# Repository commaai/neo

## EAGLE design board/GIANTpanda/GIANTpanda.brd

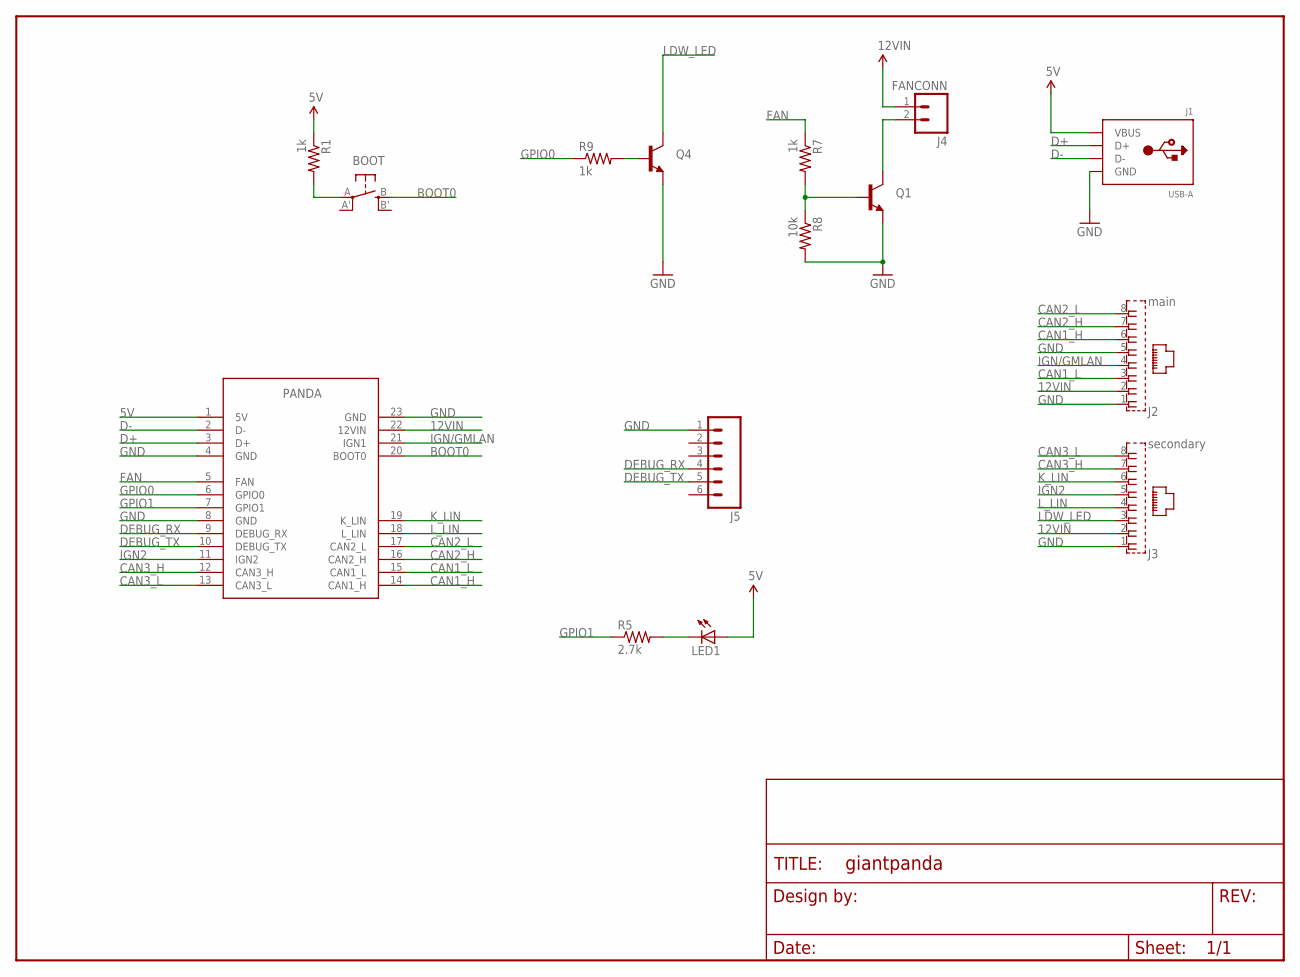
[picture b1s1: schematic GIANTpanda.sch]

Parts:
BOOT: SPST_TACT-EVQQ2; EVQ-Q2
FRAME1: FRAME-LETTERNO_PACKAGE; DUMMY
J1: USB-A; MOLEX_480371000
J2: main; GLX-S-88M
J3: secondary; GLX-S-88M
J4: FANCONN; 1.25CONN
J5: M06NO_SILK_YES_STOP; 1X06_NO_SILK_YES_STOP
LED1: LEDCHIPLED_0805; CHIPLED_0805
Q1, Q4: MMBT2222A; SOT23-3
R1, R7, R9: 1k; 0603-R
R5: 2.7k; 0603-R
R8: 10k; 0603-R
U$1: PANDA; PANDA-FOOT

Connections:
5V: J1.1 (VBUS), LED1.A, R1.1, U$1.1 (5V)
12VIN: J2.2, J3.2, J4.1, U$1.22 (12VIN)
BOOT0: BOOT.B (S), U$1.20 (BOOT0)
CAN1_H: J2.6, U$1.14 (CAN1_H)
CAN1_L: J2.3, U$1.15 (CAN1_L)
CAN2_H: J2.7, U$1.16 (CAN2_H)
CAN2_L: J2.8, U$1.17 (CAN2_L)
CAN3_H: J3.7, U$1.12 (CAN3_H)
CAN3_L: J3.8, U$1.13 (CAN3_L)
D+: J1.3 (D+), U$1.3 (D+)
D-: J1.2 (D-), U$1.2 (D-)
DEBUG_RX: J5.4, U$1.9 (DEBUG_RX)
DEBUG_TX: J5.5, U$1.10 (DEBUG_TX)
FAN: R7.1, U$1.5 (FAN)
GND: J1.4 (GND), J2.1, J2.5, J3.1, J5.1, Q1.2 (E), Q4.2 (E), R8.2, U$1.4 (GND), U$1.8 (GND), U$1.23 (GND)
GPIO0: R9.1, U$1.6 (GPIO0)
GPIO1: R5.1, U$1.7 (GPIO1)
IGN2: J3.5, U$1.11 (IGN2)
IGN/GMLAN: J2.4, U$1.21 (IGN1)
K_LIN: J3.6, U$1.19 (K_LIN)
LDW_LED: J3.3, Q4.3 (C)
L_LIN: J3.4, U$1.18 (L_LIN)
unnamed: BOOT.A, R1.2
unnamed: LED1.C, R5.2
unnamed: J4.2, Q1.3 (C)
unnamed: Q1.1 (B), R7.2, R8.1
unnamed: Q4.1 (B), R9.2

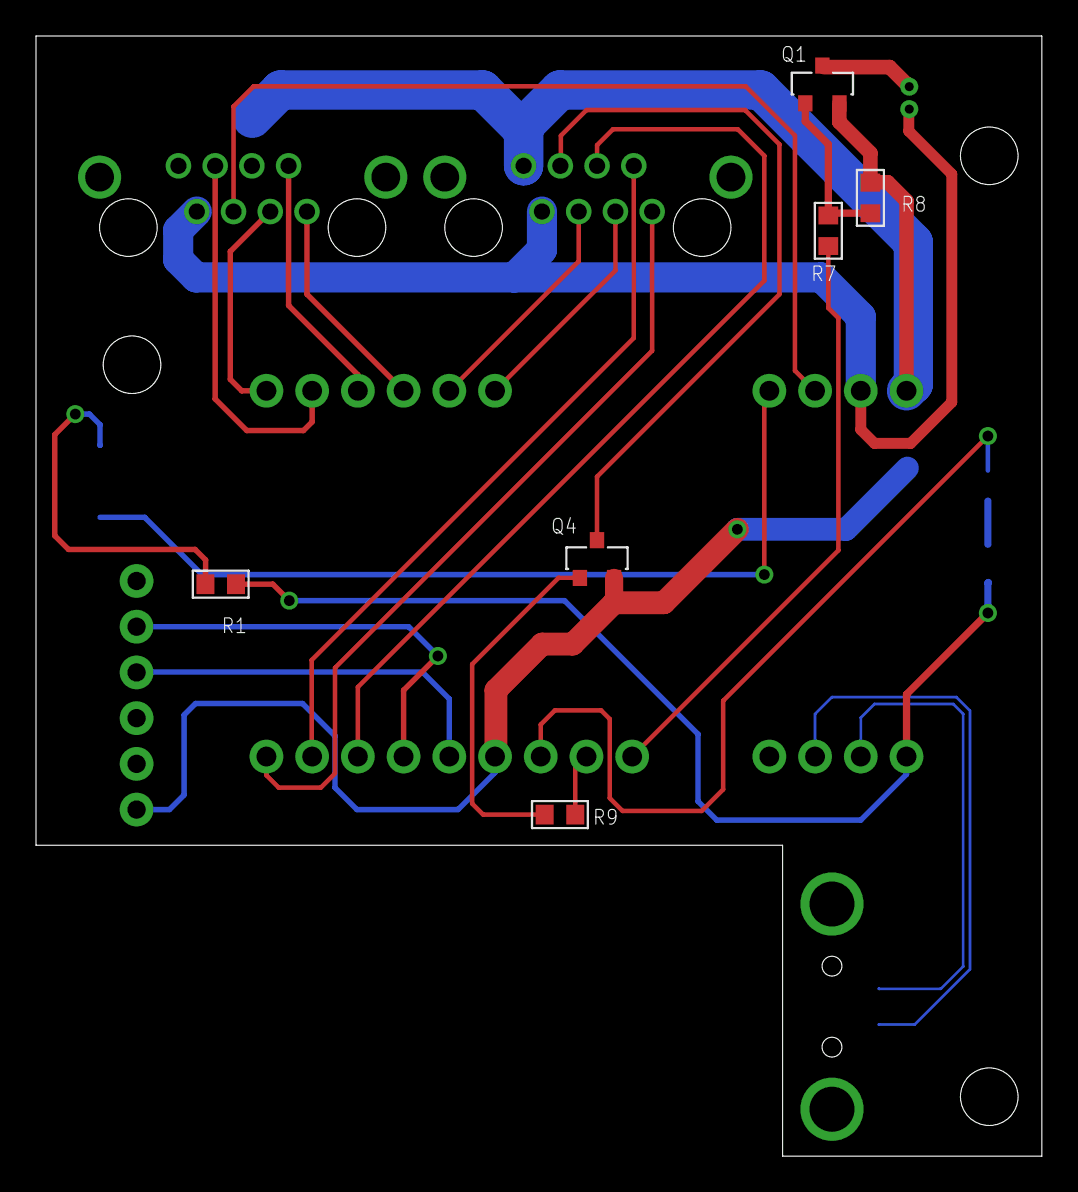
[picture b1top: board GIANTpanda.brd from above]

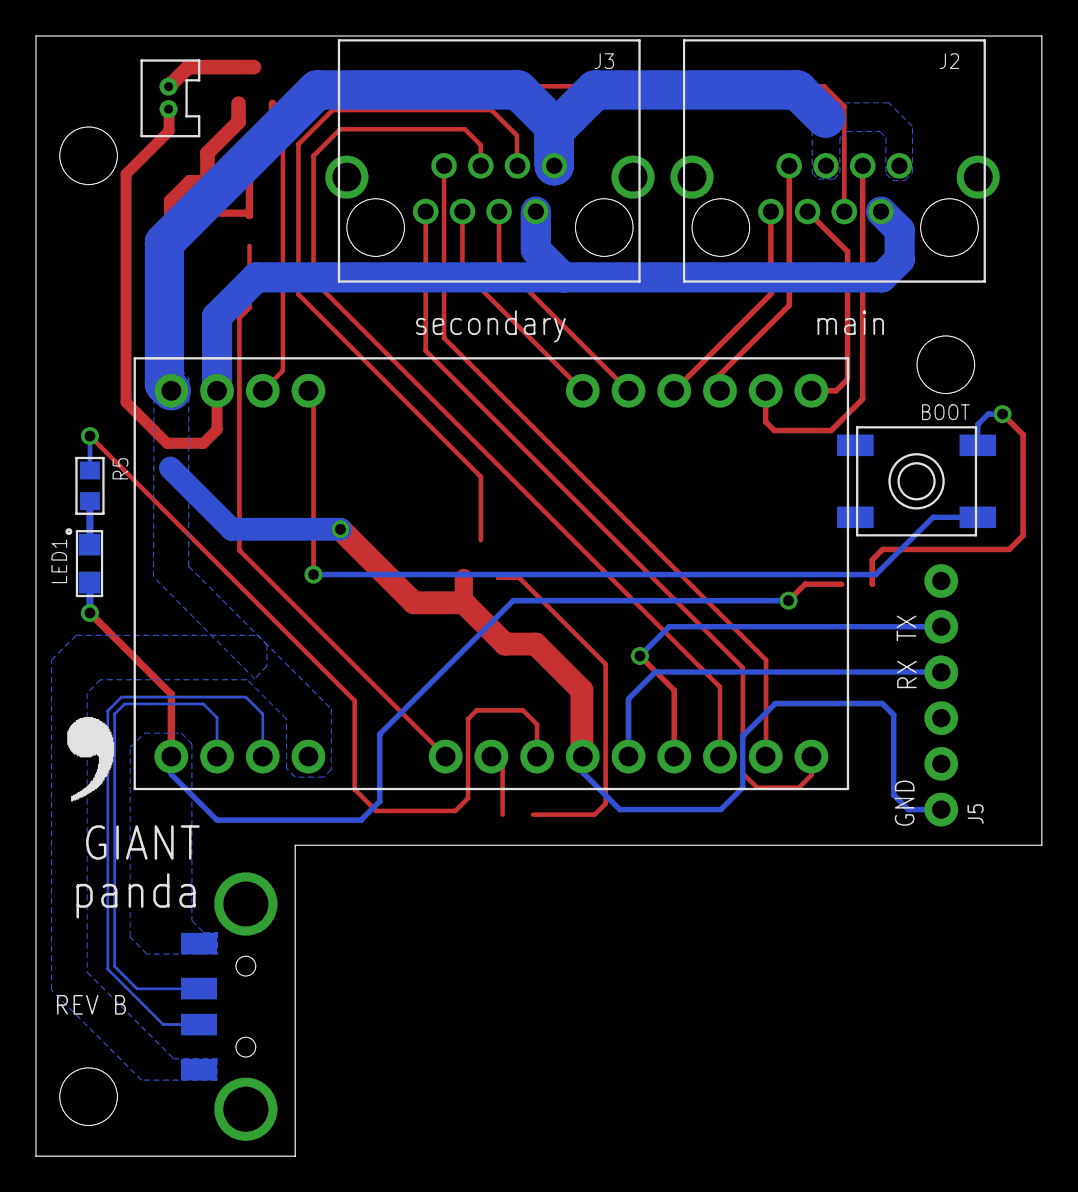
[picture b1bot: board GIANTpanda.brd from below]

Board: 2 copper layers, 55.9 x 62.2 mm, 17 parts (9 on the bottom side), 27 nets.

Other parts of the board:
U$2: LOGO

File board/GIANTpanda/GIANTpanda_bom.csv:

digikey part num,order qty,qty used,ref des,value,footprint
1175-1008-ND,1,1,J1,usb a,smd-4
AE10398-ND,2,2,"J2, J3",rj45,thru hole-8
WM1731-ND ,1,1,J4,fan connector,thru hole-2
S1011EC-40-ND,1,1,J5,uart connector,thru hole-6
475-1410-1-ND,2,1,LED1,green,0805
MMBT2222ALT1GOSCT-ND,3,2,"Q1, Q4",mmbt2222a,sot23-3
311-10KGRCT-ND,10,1,R8,10k,0603
311-1.0KGRCT-ND,10,3,"R1, R7, R9",1k,0603
311-2.7KGRCT-ND,10,1,R5,2.7k,0603
P12961SCT-ND,1,1,SW1,spst,smd-4

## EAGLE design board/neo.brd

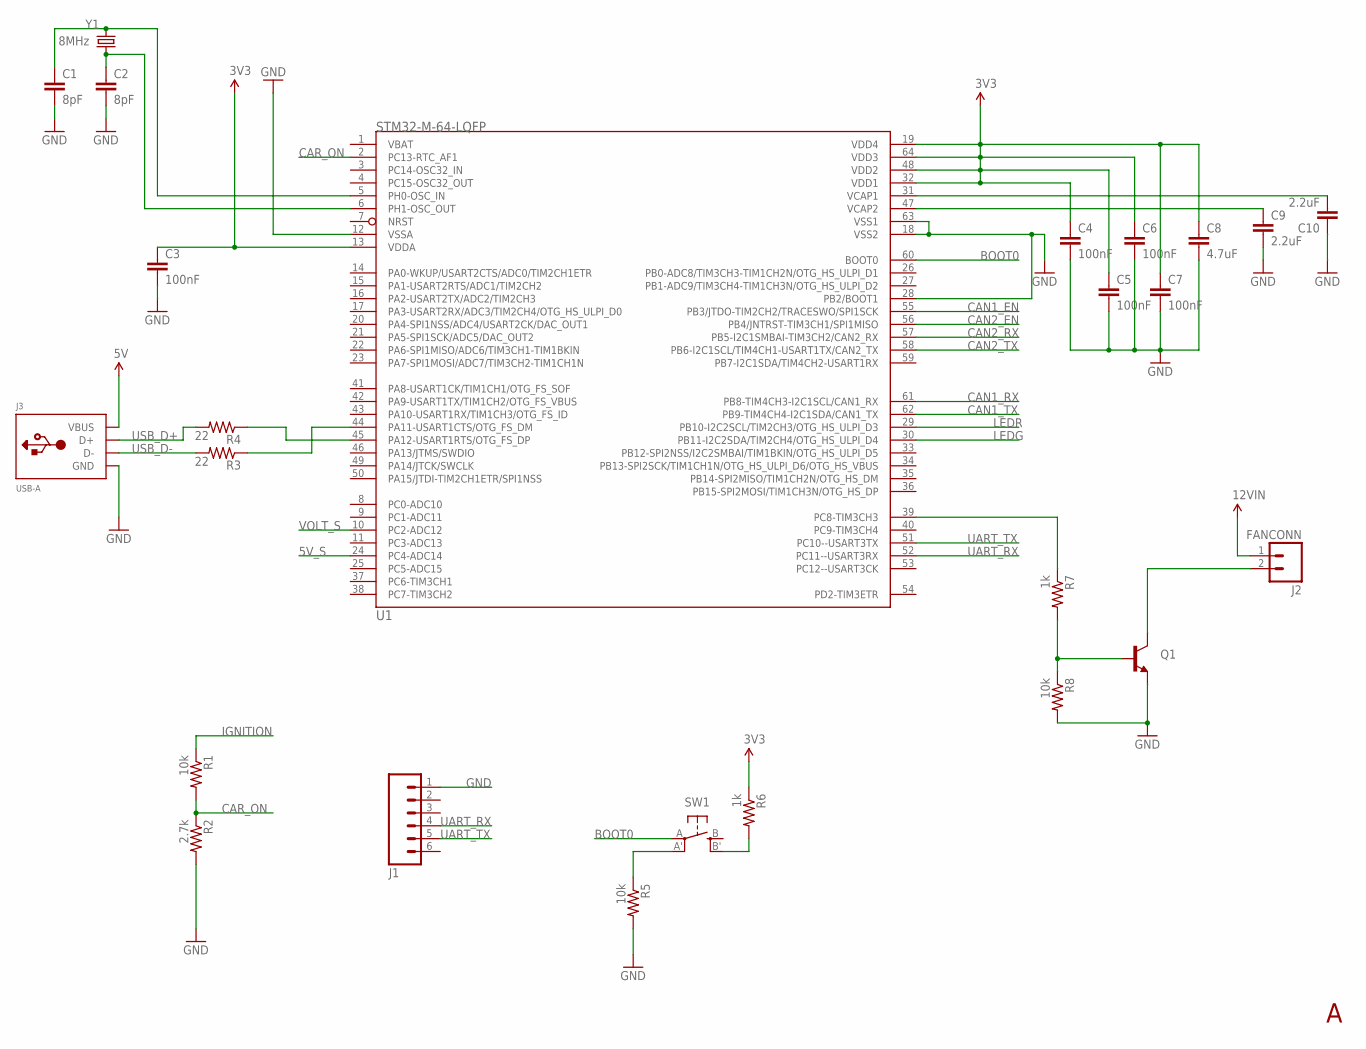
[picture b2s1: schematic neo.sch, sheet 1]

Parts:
C1, C2: 8pF; 0603-CAP
C3, C4, C5, C6, C7: 100nF; 0603-CAP
C8: 4.7uF; 0603-CAP
C9, C10: 2.2uF; 0603-CAP
J1: M06NO_SILK_YES_STOP; 1X06_NO_SILK_YES_STOP
J2: FANCONN; 1.25CONN
J3: USB-A; MOLEX_480371000
Q1: MMBT2222A; SOT23-3
R1, R5, R8: 10k; R0603
R2: 2.7k; R0603
R3, R4: 22; R0603
R6, R7: 1k; R0603
SW1: SPST_TACT-EVQQ2; EVQ-Q2
U1: STM32-M-64-LQFP; LQFP64
Y1: 8MHz; CRYSTAL-TXC-7A

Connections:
3V3: C3.1, C4.1, C5.1, C6.1, C7.1, C8.1, R6.1, U1.13 (VDDA), U1.19 (VDD4), U1.32 (VDD1), U1.48 (VDD2), U1.64 (VDD3); also elsewhere on the board
5V: J3.1 (VBUS); also elsewhere on the board
5V_S: U1.24 (PC4-ADC14); also elsewhere on the board
12VIN: J2.1; also elsewhere on the board
BOOT0: SW1.A, U1.60 (BOOT0)
CAN1_EN: U1.55 (PB3/JTDO-TIM2CH2/TRACESWO/SPI1SCK); also elsewhere on the board
CAN1_RX: U1.61 (PB8-TIM4CH3-I2C1SCL/CAN1_RX); also elsewhere on the board
CAN1_TX: U1.62 (PB9-TIM4CH4-I2C1SDA/CAN1_TX); also elsewhere on the board
CAN2_EN: U1.56 (PB4/JNTRST-TIM3CH1/SPI1MISO); also elsewhere on the board
CAN2_RX: U1.57 (PB5-I2C1SMBAI-TIM3CH2/CAN2_RX); also elsewhere on the board
CAN2_TX: U1.58 (PB6-I2C1SCL/TIM4CH1-USART1TX/CAN2_TX); also elsewhere on the board
CAR_ON: R1.2, R2.1, U1.2 (PC13-RTC_AF1)
FAN_PWM: R7.1, U1.39 (PC8-TIM3CH3)
GND: C1.2, C2.2, C3.2, C4.2, C5.2, C6.2, C7.2, C8.2, C9.2, C10.1, J1.1, J3.4 (GND), Q1.2 (E), R2.2, R5.2, R8.2, U1.12 (VSSA), U1.18 (VSS2), U1.28 (PB2/BOOT1), U1.63 (VSS1); also elsewhere on the board
IGNITION: R1.1; also elsewhere on the board
LEDG: U1.30 (PB11-I2C2SDA/TIM2CH4/OTG_HS_ULPI_D4); also elsewhere on the board
LEDR: U1.29 (PB10-I2C2SCL/TIM2CH3/OTG_HS_ULPI_D3); also elsewhere on the board
unnamed: C1.1, U1.5 (PH0-OSC_IN), Y1.P$1 (1)
unnamed: C2.1, U1.6 (PH1-OSC_OUT), Y1.P$2 (2)
unnamed: R4.1, U1.45 (PA12-USART1RTS/OTG_FS_DP)
unnamed: J2.2, Q1.3 (C)
unnamed: Q1.1 (B), R7.2, R8.1
unnamed: R5.1, SW1.A' (P1)
unnamed: R6.2, SW1.B' (S1)
unnamed: R3.1, U1.44 (PA11-USART1CTS/OTG_FS_DM)
UART_RX: J1.4, U1.52 (PC11--USART3RX)
UART_TX: J1.5, U1.51 (PC10--USART3TX)
USB_D+: J3.3 (D+), R4.2
USB_D-: J3.2 (D-), R3.2
VCAP1: C10.2, U1.31 (VCAP1)
VCAP2: C9.1, U1.47 (VCAP2)
VOLT_S: U1.10 (PC2-ADC12); also elsewhere on the board

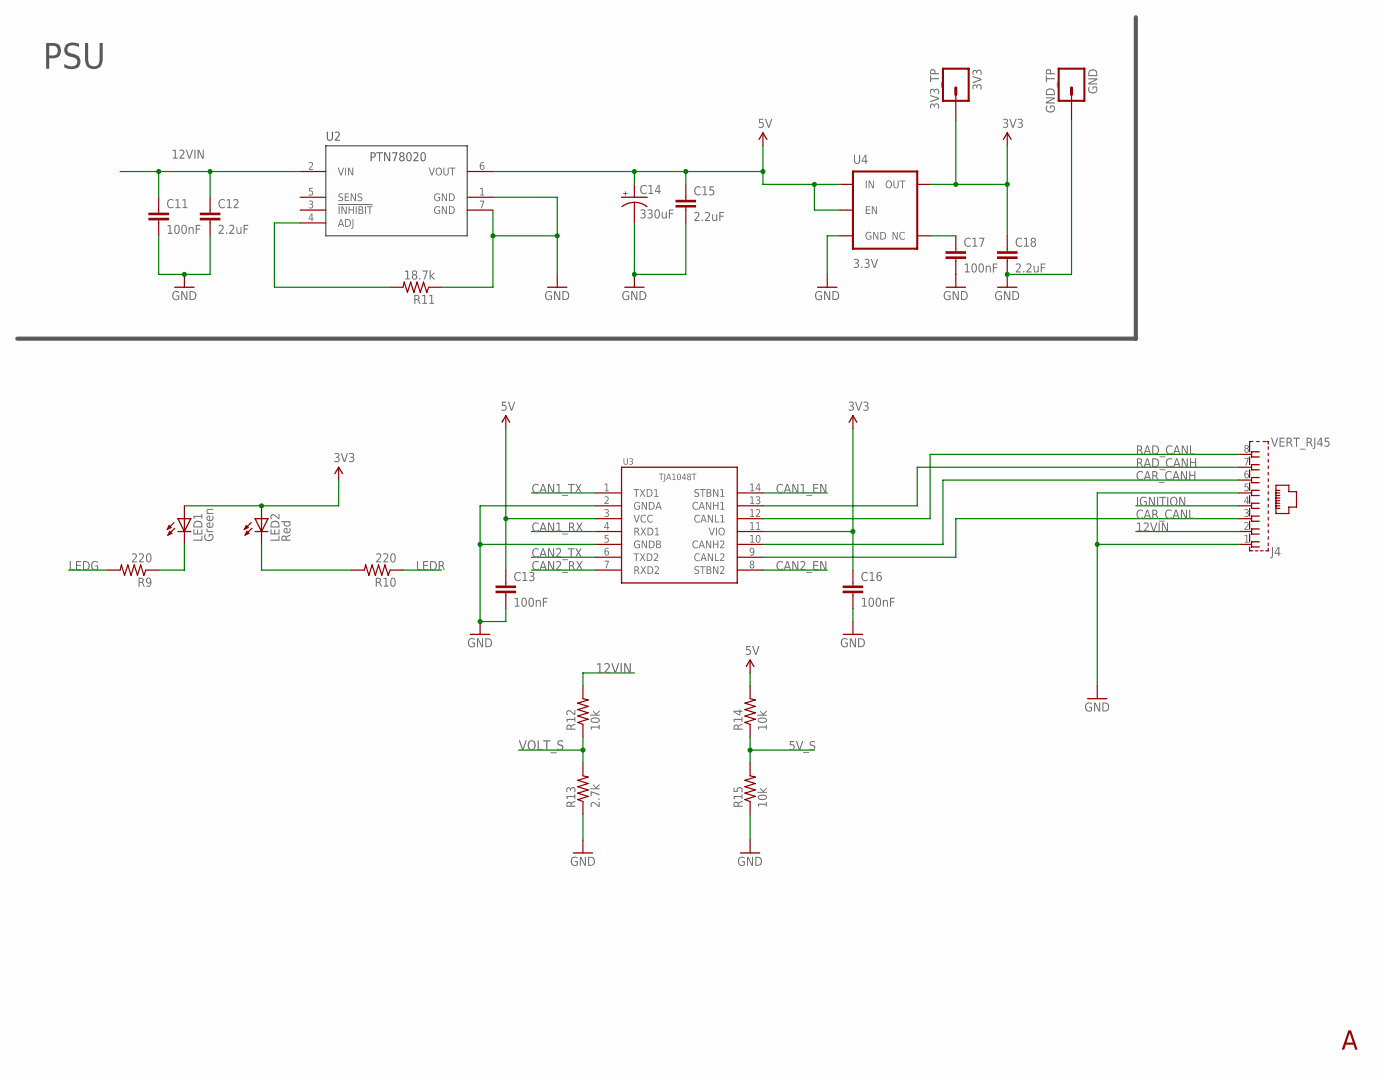
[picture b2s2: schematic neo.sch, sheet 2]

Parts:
3V3: 3V3_TP; 1X01_NO_SILK
C11, C13, C16, C17: 100nF; 0603-CAP
C12, C15: 2.2uF; 0805-CAP
C14: 330uF; E3,5-8
C18: 2.2uF; 0603-CAP
GND: GND_TP; 1X01_NO_SILK
J4: VERT_RJ45; GLX-S-88M
LED1: Green; CHIPLED_0805
LED2: Red; CHIPLED_0805
R9, R10: 220; R0603
R11: 18.7k; R0603
R12, R14, R15: 10k; R0603
R13: 2.7k; R0603
U2: PTN78020W
U3: TJA1048; SO14
U4: 3.3V; SOT23-5

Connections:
3V3: 3V3.1, C16.1, C18.1, LED1.A, LED2.A, U3.11 (VIO), U4.5 (OUT); also elsewhere on the board
5V: C13.1, C14.+, C15.1, R14.2, U2.6 (VOUT), U3.3 (VCC), U4.1 (IN), U4.3 (EN); also elsewhere on the board
5V_S: R14.1, R15.2; also elsewhere on the board
12VIN: C11.1, C12.1, J4.2, R12.2, U2.2 (VIN); also elsewhere on the board
CAN1_EN: U3.14 (STBN1); also elsewhere on the board
CAN1_RX: U3.4 (RXD1); also elsewhere on the board
CAN1_TX: U3.1 (TXD1); also elsewhere on the board
CAN2_EN: U3.8 (STBN2); also elsewhere on the board
CAN2_RX: U3.7 (RXD2); also elsewhere on the board
CAN2_TX: U3.6 (TXD2); also elsewhere on the board
CAR_CANH: J4.6, U3.10 (CANH2)
CAR_CANL: J4.3, U3.9 (CANL2)
GND: C11.2, C12.2, C13.2, C14.-, C15.2, C16.2, C17.2, C18.2, GND.1, J4.1, J4.5, R11.1, R13.1, R15.1, U2.1 (GND), U2.7 (GND), U3.2 (GNDA), U3.5 (GNDB), U4.2 (GND); also elsewhere on the board
IGNITION: J4.4; also elsewhere on the board
LEDG: R9.2; also elsewhere on the board
LEDR: R10.1; also elsewhere on the board
unnamed: LED2.C, R10.2
unnamed: LED1.C, R9.1
unnamed: R11.2, U2.4 (ADJ)
unnamed: C17.1, U4.4 (NC)
RAD_CANH: J4.7, U3.13 (CANH1)
RAD_CANL: J4.8, U3.12 (CANL1)
VOLT_S: R12.1, R13.2; also elsewhere on the board

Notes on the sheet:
PSU

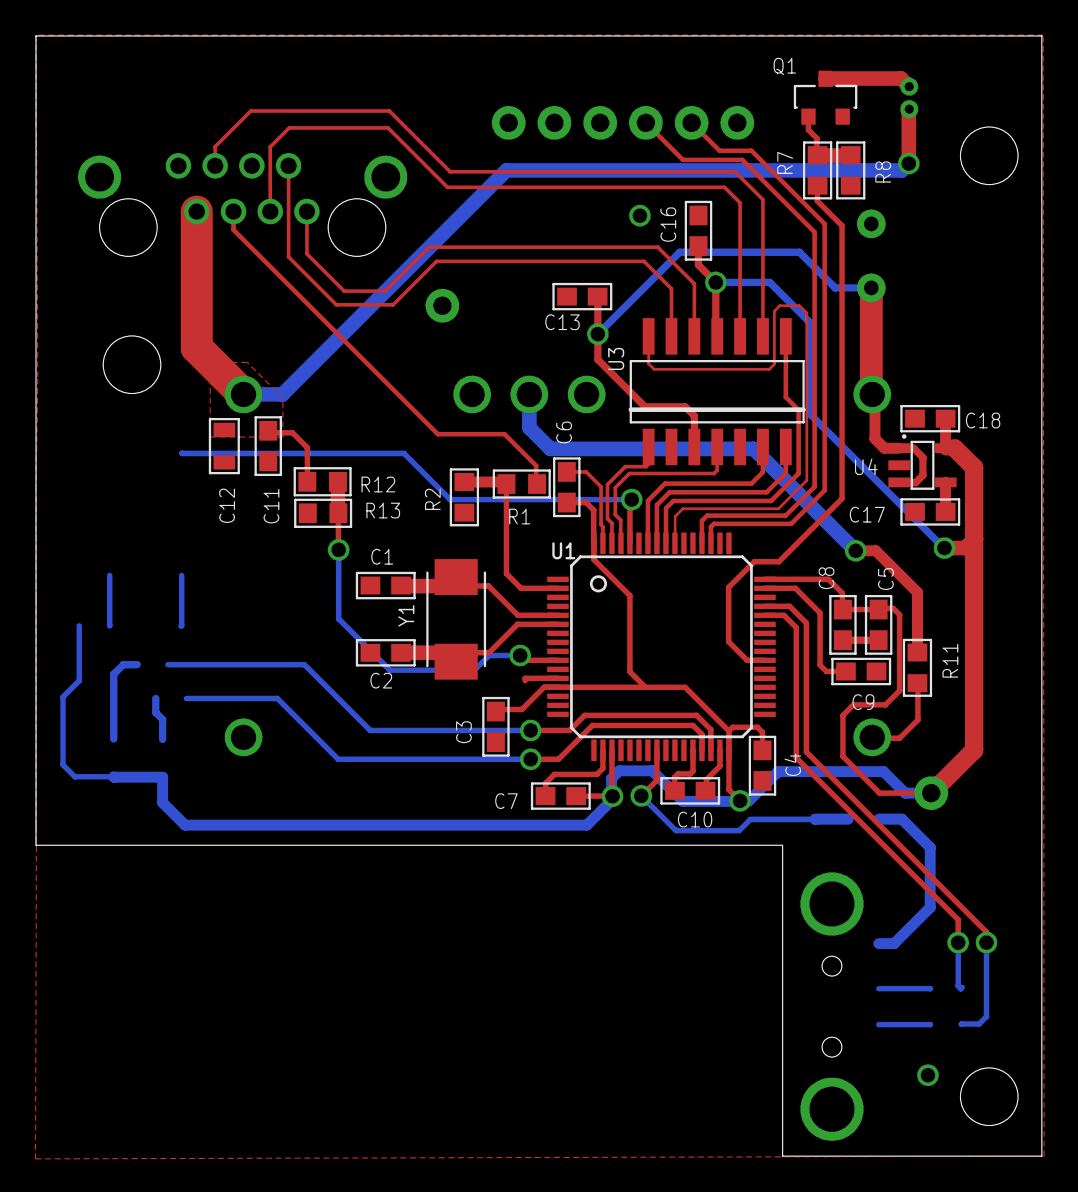
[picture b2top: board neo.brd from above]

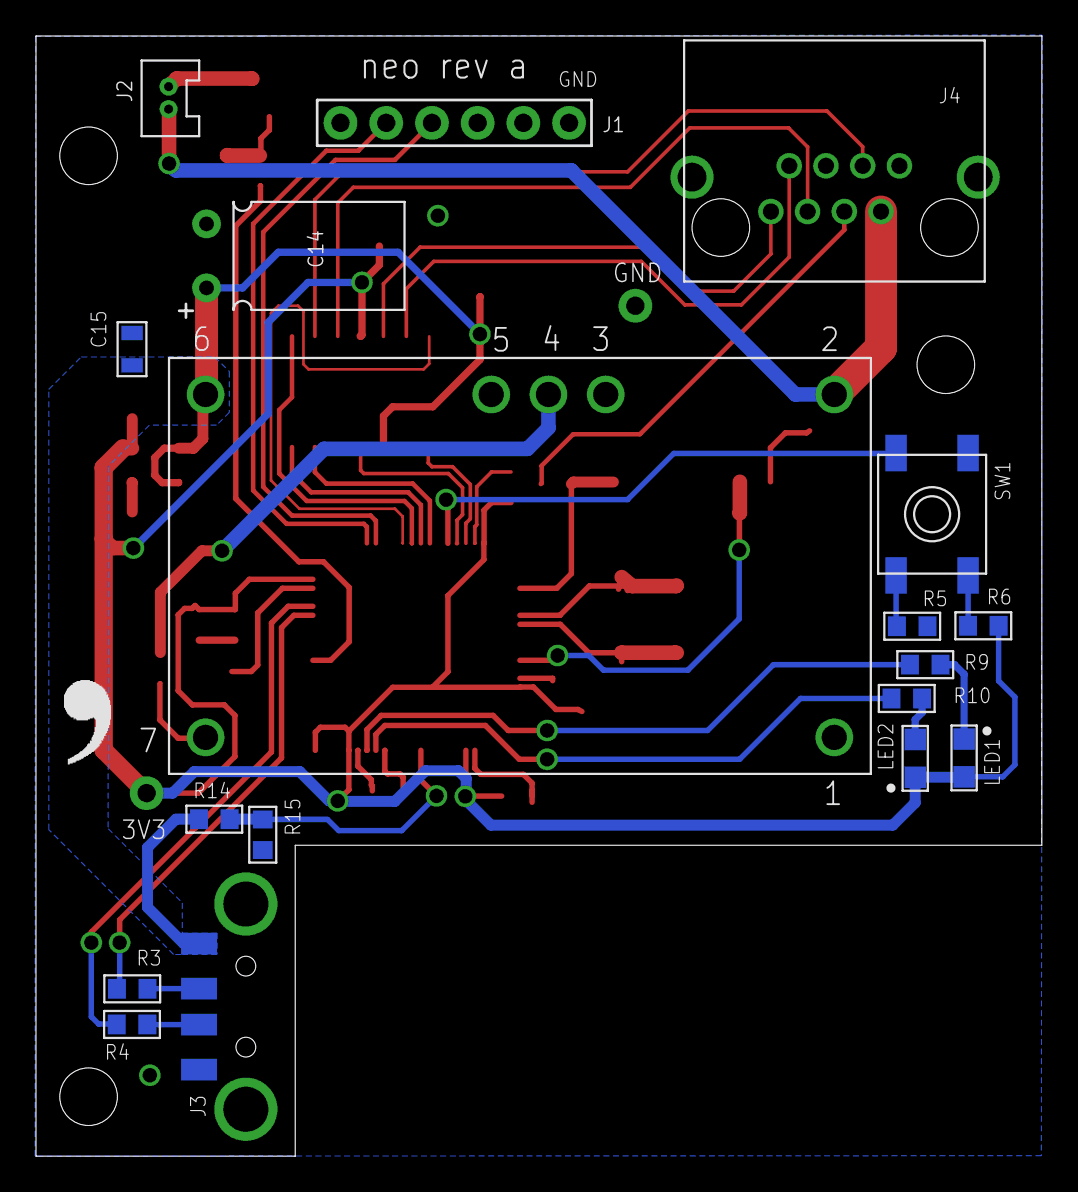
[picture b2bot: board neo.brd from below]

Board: 2 copper layers, 55.9 x 62.2 mm, 49 parts (19 on the bottom side), 40 nets.

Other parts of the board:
U$1: LOGO

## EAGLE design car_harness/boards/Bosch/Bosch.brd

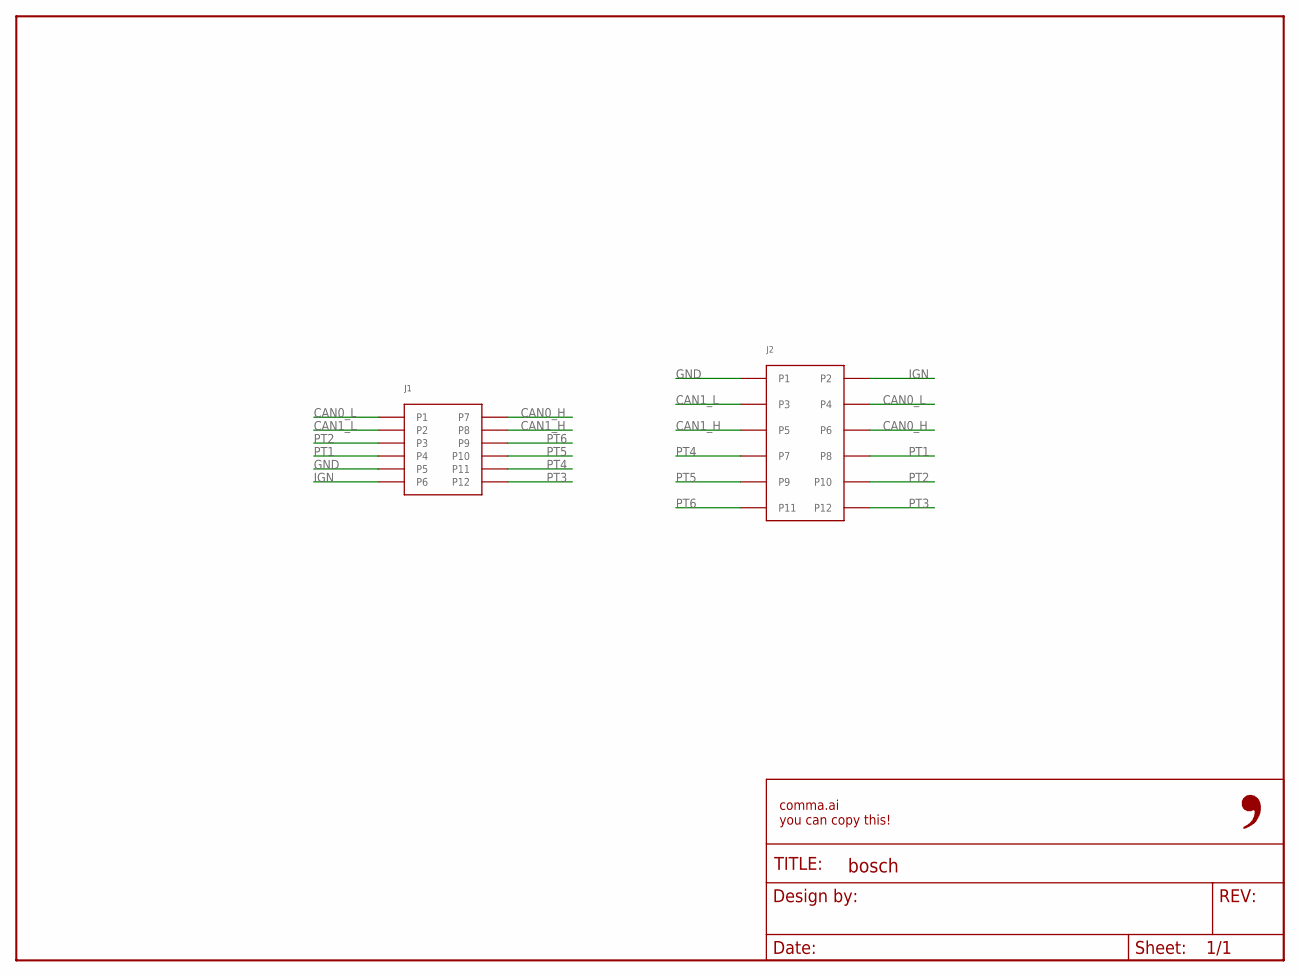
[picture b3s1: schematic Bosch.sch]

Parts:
FRAME1: FRAME-LETTER-OPENNO_PACKAGE; DUMMY
J1: MX34M12NF1; MPN MX34M12NF1
J2: 5018761240; MPN 5018761240

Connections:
CAN0_H: J1.P7, J2.P6
CAN0_L: J1.P1, J2.P4
CAN1_H: J1.P8, J2.P5
CAN1_L: J1.P2, J2.P3
GND: J1.P5, J2.P1
IGN: J1.P6, J2.P2
PT1: J1.P4, J2.P8
PT2: J1.P3, J2.P10
PT3: J1.P12, J2.P12
PT4: J1.P11, J2.P7
PT5: J1.P10, J2.P9
PT6: J1.P9, J2.P11

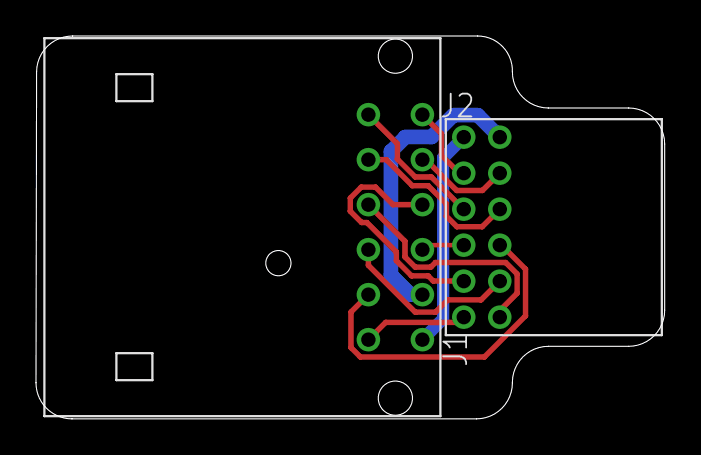
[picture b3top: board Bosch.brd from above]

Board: 2 copper layers, 34.9 x 21.3 mm, 4 parts (1 on the bottom side), 12 nets.

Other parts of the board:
E$1: LOGO

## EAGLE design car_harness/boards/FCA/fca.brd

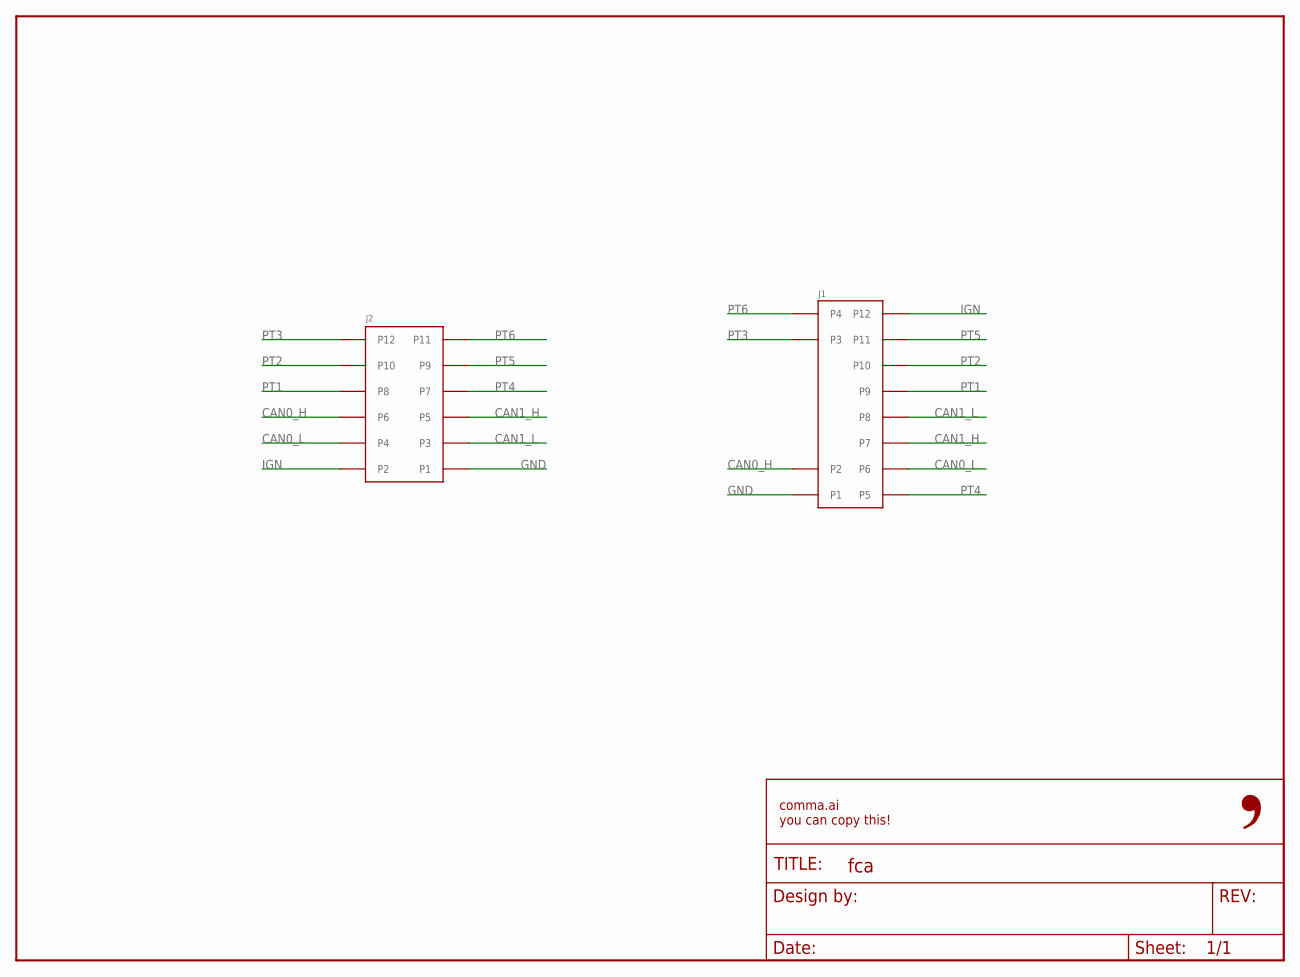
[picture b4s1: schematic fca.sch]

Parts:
FRAME1: FRAME-LETTER-OPENNO_PACKAGE; DUMMY
J1: 0348260124; MPN 0348260124
J2: 5018761240; MPN 5018761240

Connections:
CAN0_H: J1.P2, J2.P6
CAN0_L: J1.P6, J2.P4
CAN1_H: J1.P7, J2.P5
CAN1_L: J1.P8, J2.P3
GND: J1.P1, J2.P1
IGN: J1.P12, J2.P2
PT1: J1.P9, J2.P8
PT2: J1.P10, J2.P10
PT3: J1.P3, J2.P12
PT4: J1.P5, J2.P7
PT5: J1.P11, J2.P9
PT6: J1.P4, J2.P11

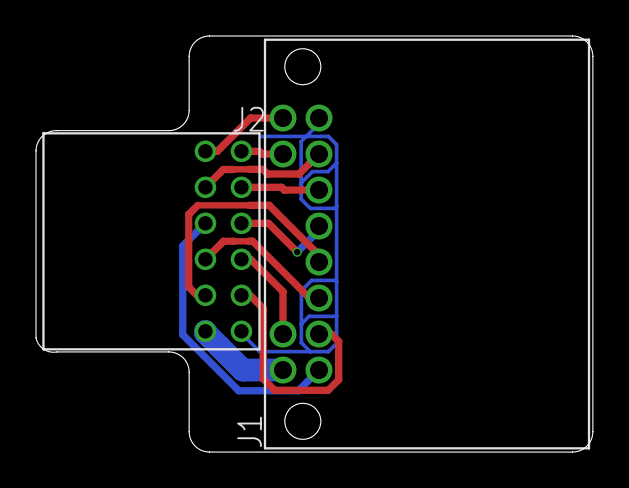
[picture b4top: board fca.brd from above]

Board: 2 copper layers, 30.9 x 23.1 mm, 4 parts (1 on the bottom side), 12 nets.

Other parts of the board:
U$1: LOGO

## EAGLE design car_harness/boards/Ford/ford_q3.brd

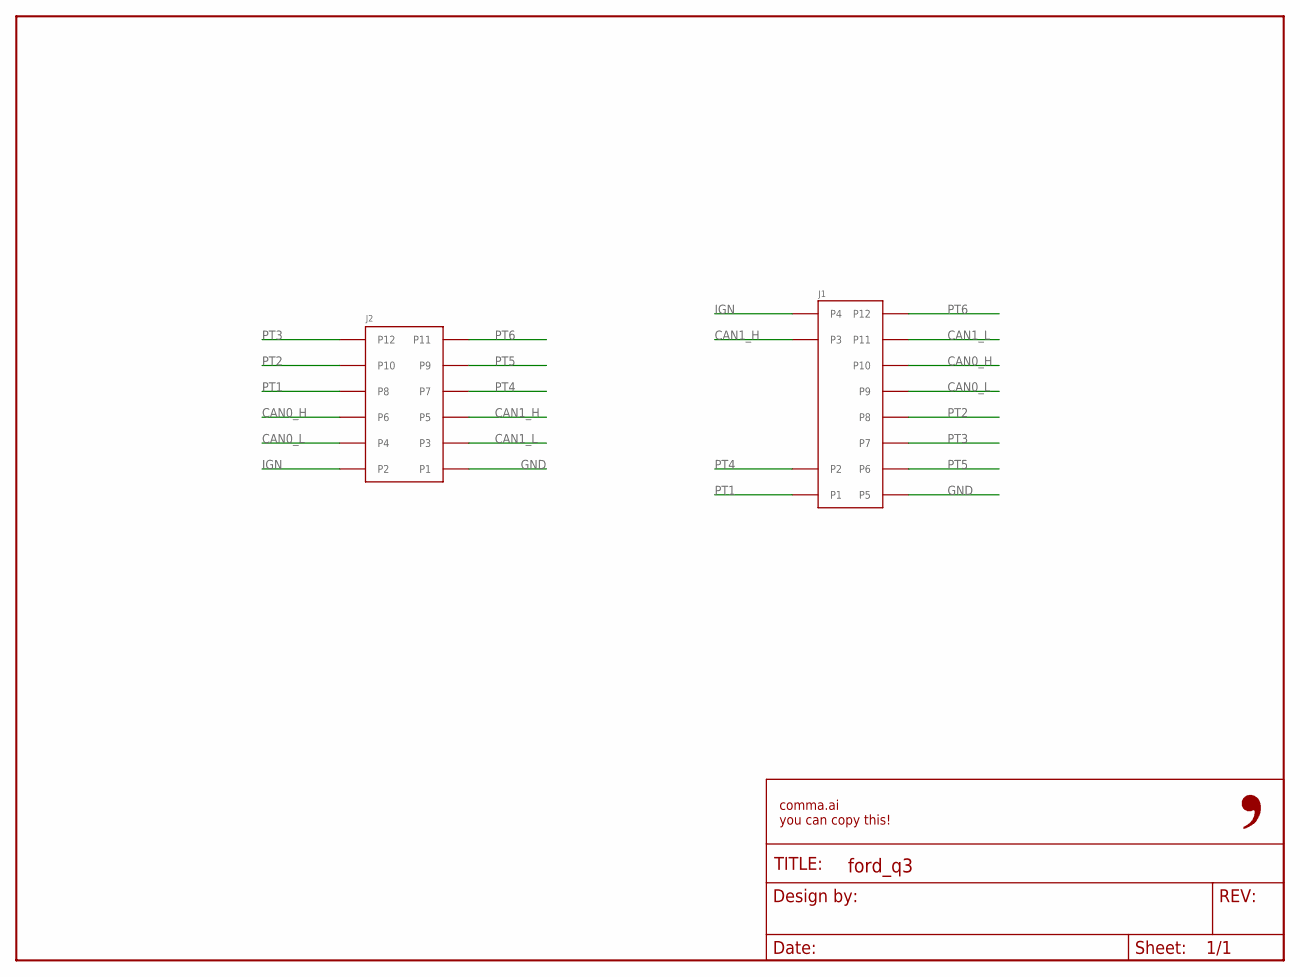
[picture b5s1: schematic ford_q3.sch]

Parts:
FRAME1: FRAME-LETTER-OPENNO_PACKAGE; DUMMY
J1: 0348260124; MPN 0348260124
J2: 5018761240; MPN 5018761240

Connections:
CAN0_H: J1.P10, J2.P6
CAN0_L: J1.P9, J2.P4
CAN1_H: J1.P3, J2.P5
CAN1_L: J1.P11, J2.P3
GND: J1.P5, J2.P1
IGN: J1.P4, J2.P2
PT1: J1.P1, J2.P8
PT2: J1.P8, J2.P10
PT3: J1.P7, J2.P12
PT4: J1.P2, J2.P7
PT5: J1.P6, J2.P9
PT6: J1.P12, J2.P11

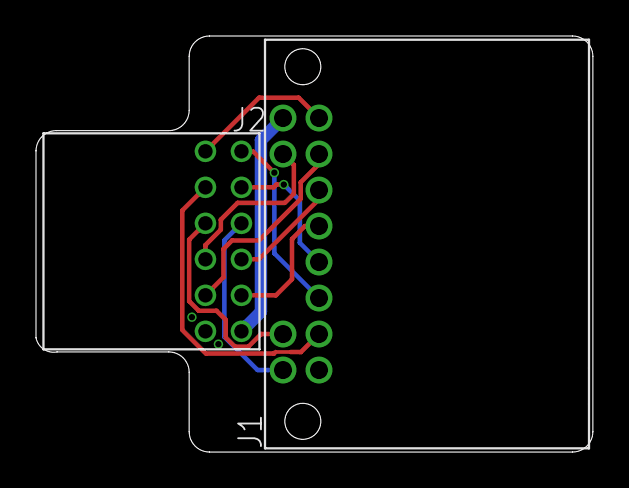
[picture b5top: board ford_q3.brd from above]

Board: 2 copper layers, 30.9 x 23.1 mm, 4 parts (1 on the bottom side), 12 nets.

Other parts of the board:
U$1: LOGO

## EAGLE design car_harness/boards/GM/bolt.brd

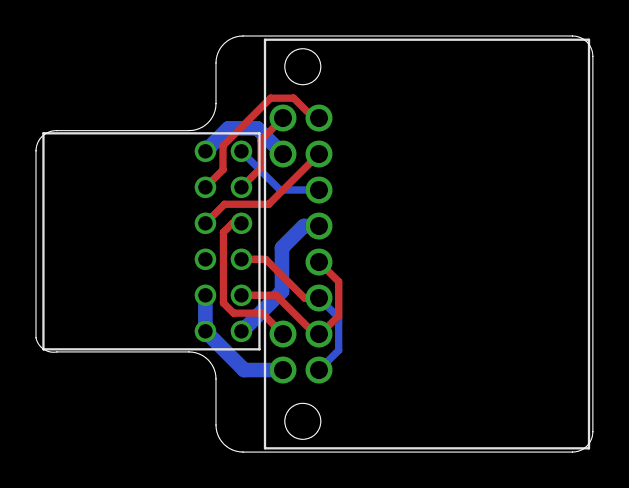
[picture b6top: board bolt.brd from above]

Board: 2 copper layers, 30.9 x 23.1 mm, 4 parts (1 on the bottom side), 10 nets.

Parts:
FRAME1: FRAME-LETTER-OPENNO_PACKAGE; DUMMY
J1: 0348260124
J2: 5018761240
U$1: LOGO

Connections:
12VIN: J1.P3, J2.P11
CAN0_H: J1.P5, J1.P7, J2.P6
CAN0_L: J1.P6, J1.P8, J2.P4
GND: J1.P1, J2.P1, J2.P3
IGN: J1.P9, J2.P2
PT1: J1.P2, J2.P8
PT2: J1.P4, J2.P10
PT3: J1.P10, J2.P12
PT4: J1.P11, J2.P7
PT5: J1.P12, J2.P9

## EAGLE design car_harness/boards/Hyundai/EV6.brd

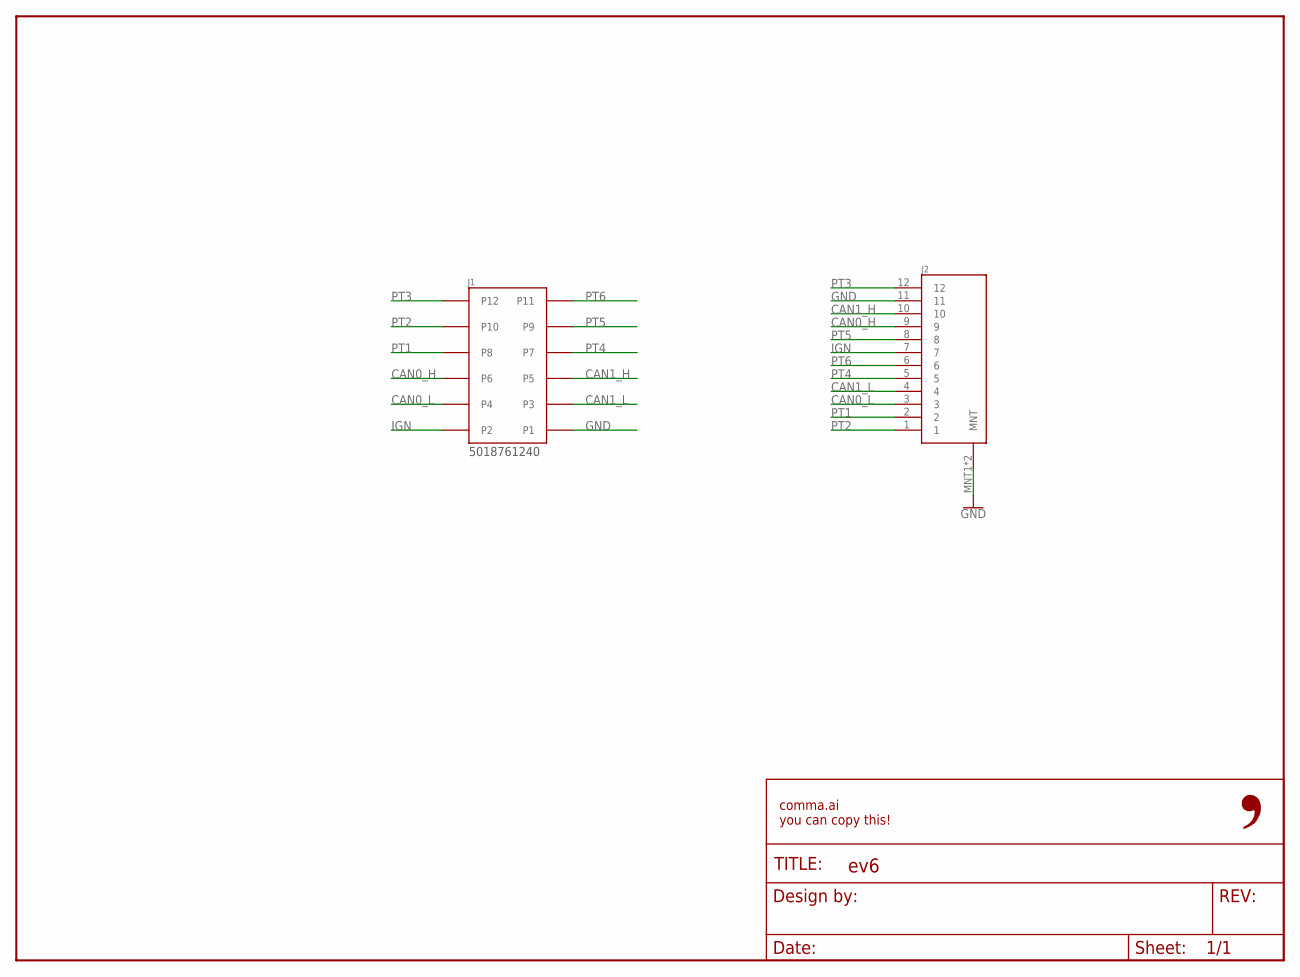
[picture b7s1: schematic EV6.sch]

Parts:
FRAME1: FRAME-LETTER-OPENNO_PACKAGE; DUMMY
J1: 5018761240; MPN 5018761240
J2: MG646151; MPN MG646151-5

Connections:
CAN0_H: J1.P6, J2.9
CAN0_L: J1.P4, J2.3
CAN1_H: J1.P5, J2.10
CAN1_L: J1.P3, J2.4
GND: J1.P1, J2.11, J2.MNT1 (MNT), J2.MNT2 (MNT)
IGN: J1.P2, J2.7
PT1: J1.P8, J2.2
PT2: J1.P10, J2.1
PT3: J1.P12, J2.12
PT4: J1.P7, J2.5
PT5: J1.P9, J2.8
PT6: J1.P11, J2.6

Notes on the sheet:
5018761240

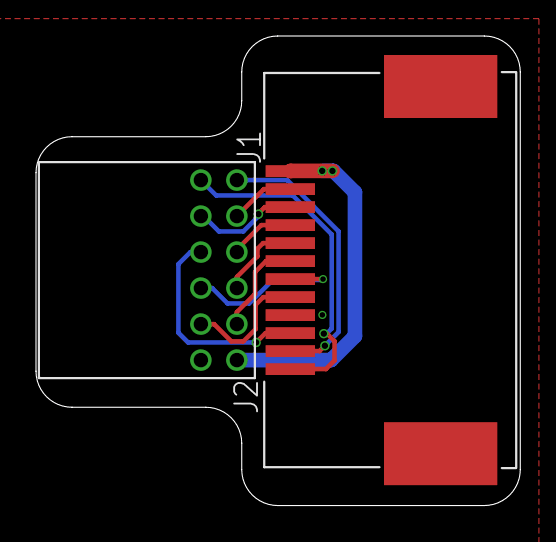
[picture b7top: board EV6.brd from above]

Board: 2 copper layers, 26.9 x 26.1 mm, 4 parts (1 on the bottom side), 12 nets.

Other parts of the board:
U$1: LOGO

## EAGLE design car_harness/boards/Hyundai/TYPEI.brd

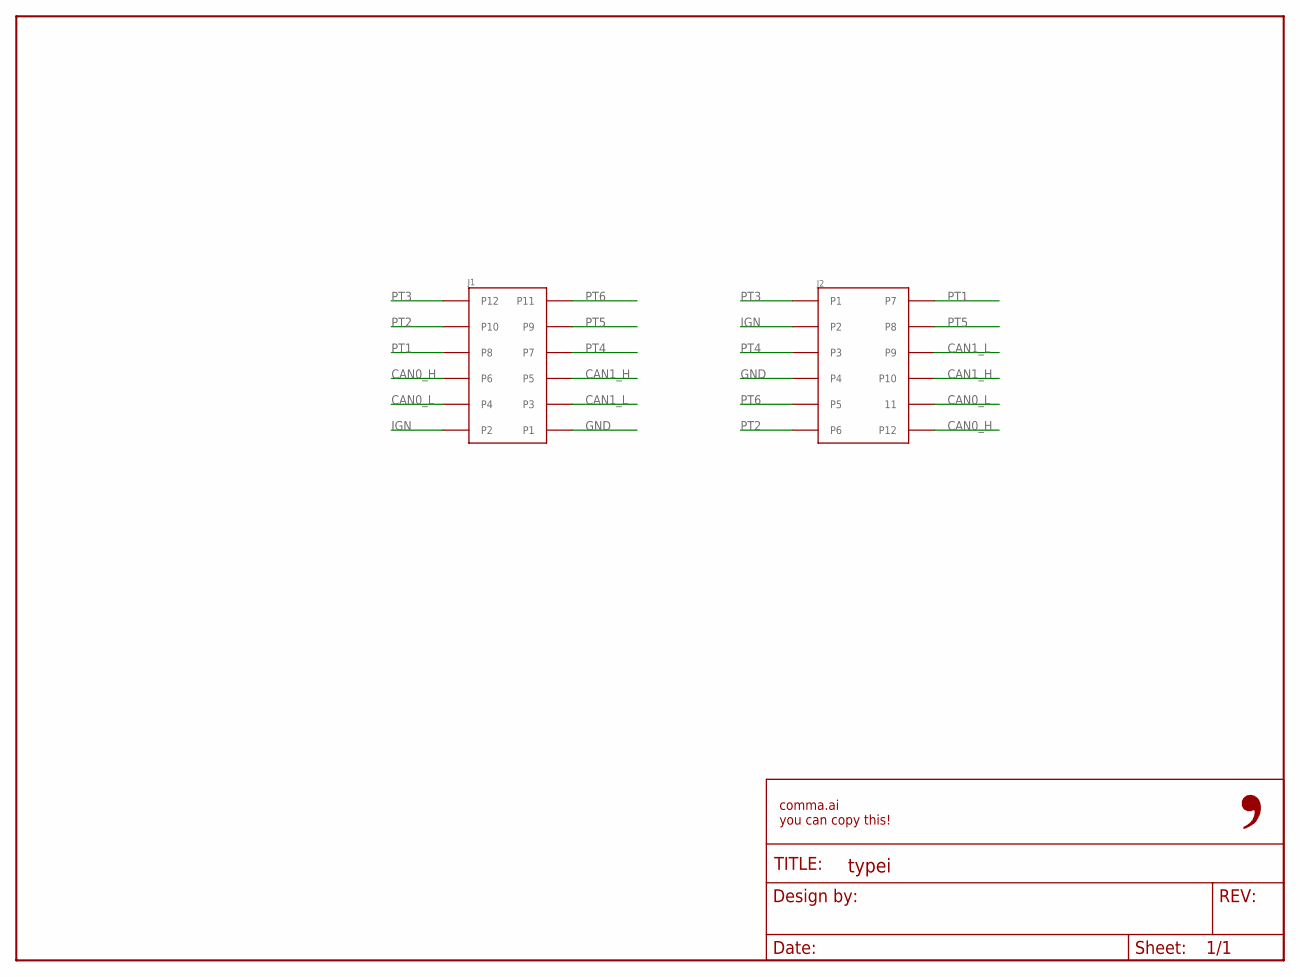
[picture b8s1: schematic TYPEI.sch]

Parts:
FRAME1: FRAME-LETTER-OPENNO_PACKAGE; DUMMY
J1: 5018761240; MPN 5018761240
J2: MG645845; MPN MG645845

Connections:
CAN0_H: J1.P6, J2.P12
CAN0_L: J1.P4, J2.P11 (11)
CAN1_H: J1.P5, J2.P10
CAN1_L: J1.P3, J2.P9
GND: J1.P1, J2.P4
IGN: J1.P2, J2.P2
PT1: J1.P8, J2.P7
PT2: J1.P10, J2.P6
PT3: J1.P12, J2.P1
PT4: J1.P7, J2.P3
PT5: J1.P9, J2.P8
PT6: J1.P11, J2.P5

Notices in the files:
parts and their libraries:
SparkFun-Aesthetics: Licensing: Creative Commons ShareAlike 4.0 International - https://creativecommons.org/licenses/by-sa/4.0
SparkFun-Aesthetics: Released under the Creative Commons Attribution Share-Alike 4.0 License
SparkFun-Aesthetics: https://creativecommons.org/licenses/by-sa/4.0
